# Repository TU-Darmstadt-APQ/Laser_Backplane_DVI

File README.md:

# Laser Head with fast Modulation Input
This repository contains the [KiCad](https://www.kicad.org/) design files for a compact laser backplane with a DVI connector for application in an ECDL laser system. The laser backplane features a fast current modulation input designed for large-bandwidth laser-frequency stabilization and a laser diode protection circuit. An additional connector for the laser piezo actuator is available.

## Laser diode protection circuit
The protection circuit consists of a relay and a reverse protection diode. The latching relay shorts the laser diode whenever the cable is disconnected or the current driver is turned off. In order to reduce the relay idle current, a latching relay and circuit are used. A fast switching transistor is used as reverse protection diode. The transistor features a very low reverse current leakage and a fast reverse recovery time.

## Fast Current Modulation
The fast modulation input consists of a Howland Current Pump complemented by a passive impedance matching network (see related work for details). It features:
- 3 dB gain flatness DC to 100 MHz
- Phase lag below 90° up to 25 MHz
- Transconductance gain of 1 mA / V
- Input voltage range ±4.8 V

**Note on the compliance voltage**
The compliance voltage of the Howland Current Pump is half of the positive output voltage swing of the operational amplifier. The circuit is implemented by a rail-to-rail output operational amplifier (ADA4807) supplied by ±5 V. Hence, the voltage at the laser diode anode is limited to 2.4 V accounting for a small head-room. Some additional head-room should be reserved for the (small) rise of the voltage required for the maximal output of the current source (5 mA). The maximal laser diode anode voltage is sufficient as a compliance voltage for infra red laser diodes. 

## Pin Configuration

Connector: DVI-I Dual Link (female)

| Pin 		| Signal 		| Description 	|
| --- 		| --- 			|	---			|
|  1 to 5 	|	NC			|				|
|  6  		|	-12 V		|	Negative supply for fast current modulation: -20 V to -5.5 V / 10 mA (max.)	|
|  7		|	EEPROM		|	Optional single wire EEPROM: AT21CS11	|
|  8  		| NC 			|				|
|  9  		| Ld-			| Laser diode cathode current pin 1/2	|
|  10  		| LD+			| Laser diode anode current pin 1/2		|
|  11  		| NC			|				|
|  12  		| Ld-			| Laser diode cathode current pin 2/2	|
|  13  		| LD+			| Laser diode anode current pin 2/2		|
|  14  		|	+12 V		| Positive supply for fast current modulation and protection circuit: 7 V to 18 V / 50 mA (max.) 	|
|  15  		| GND			| Ground reference for power supply	and modulation circuit  |
|  16  		| Relay-		| Connect to GND to switch the relay to 'laser on' state		|
|  17 to 22	| NC			| 				|
|  23  		| V_diode+		| Laser anode voltage sense connection		|
|  24  		| V_diode-		| Laser cathode voltage sense connection	|
|  C1 to C5	| NC			| 				|
|  SH		| NC			| 	Connect the shield to the laser case only			|

## Design Files
The design files can be found on the [releases](../../releases) page and include the following resources:

- Schematics as a PDF
- Gerber files
- Pick & place position files
- Bill of materials as a CSV file and also as an interactive HTML version

The latest revision of those files can be found [here](../../releases/latest).

## Related Work
Review of Scientific Instruments **93**, 063002 (2022); https://doi.org/10.1063/5.0093520

arXiv:2203.06097 [physics.optics]; [https://arxiv.org/abs/2203.06097](https://arxiv.org/abs/2203.06097)

T. Preuschoff, *Laser Technologies for Applications in Quantum Information Science*, Ph.D. thesis, TU Darmstadt, 2023, [10.26083/tuprints-00023242](10.26083/tuprints-00023242)

## License
This work is released under the CERN-OHL-W
See [https://ohwr.org/cern_ohl_w_v2.pdf](https://ohwr.org/cern_ohl_w_v2.pdf) or the included LICENSE file for more information.

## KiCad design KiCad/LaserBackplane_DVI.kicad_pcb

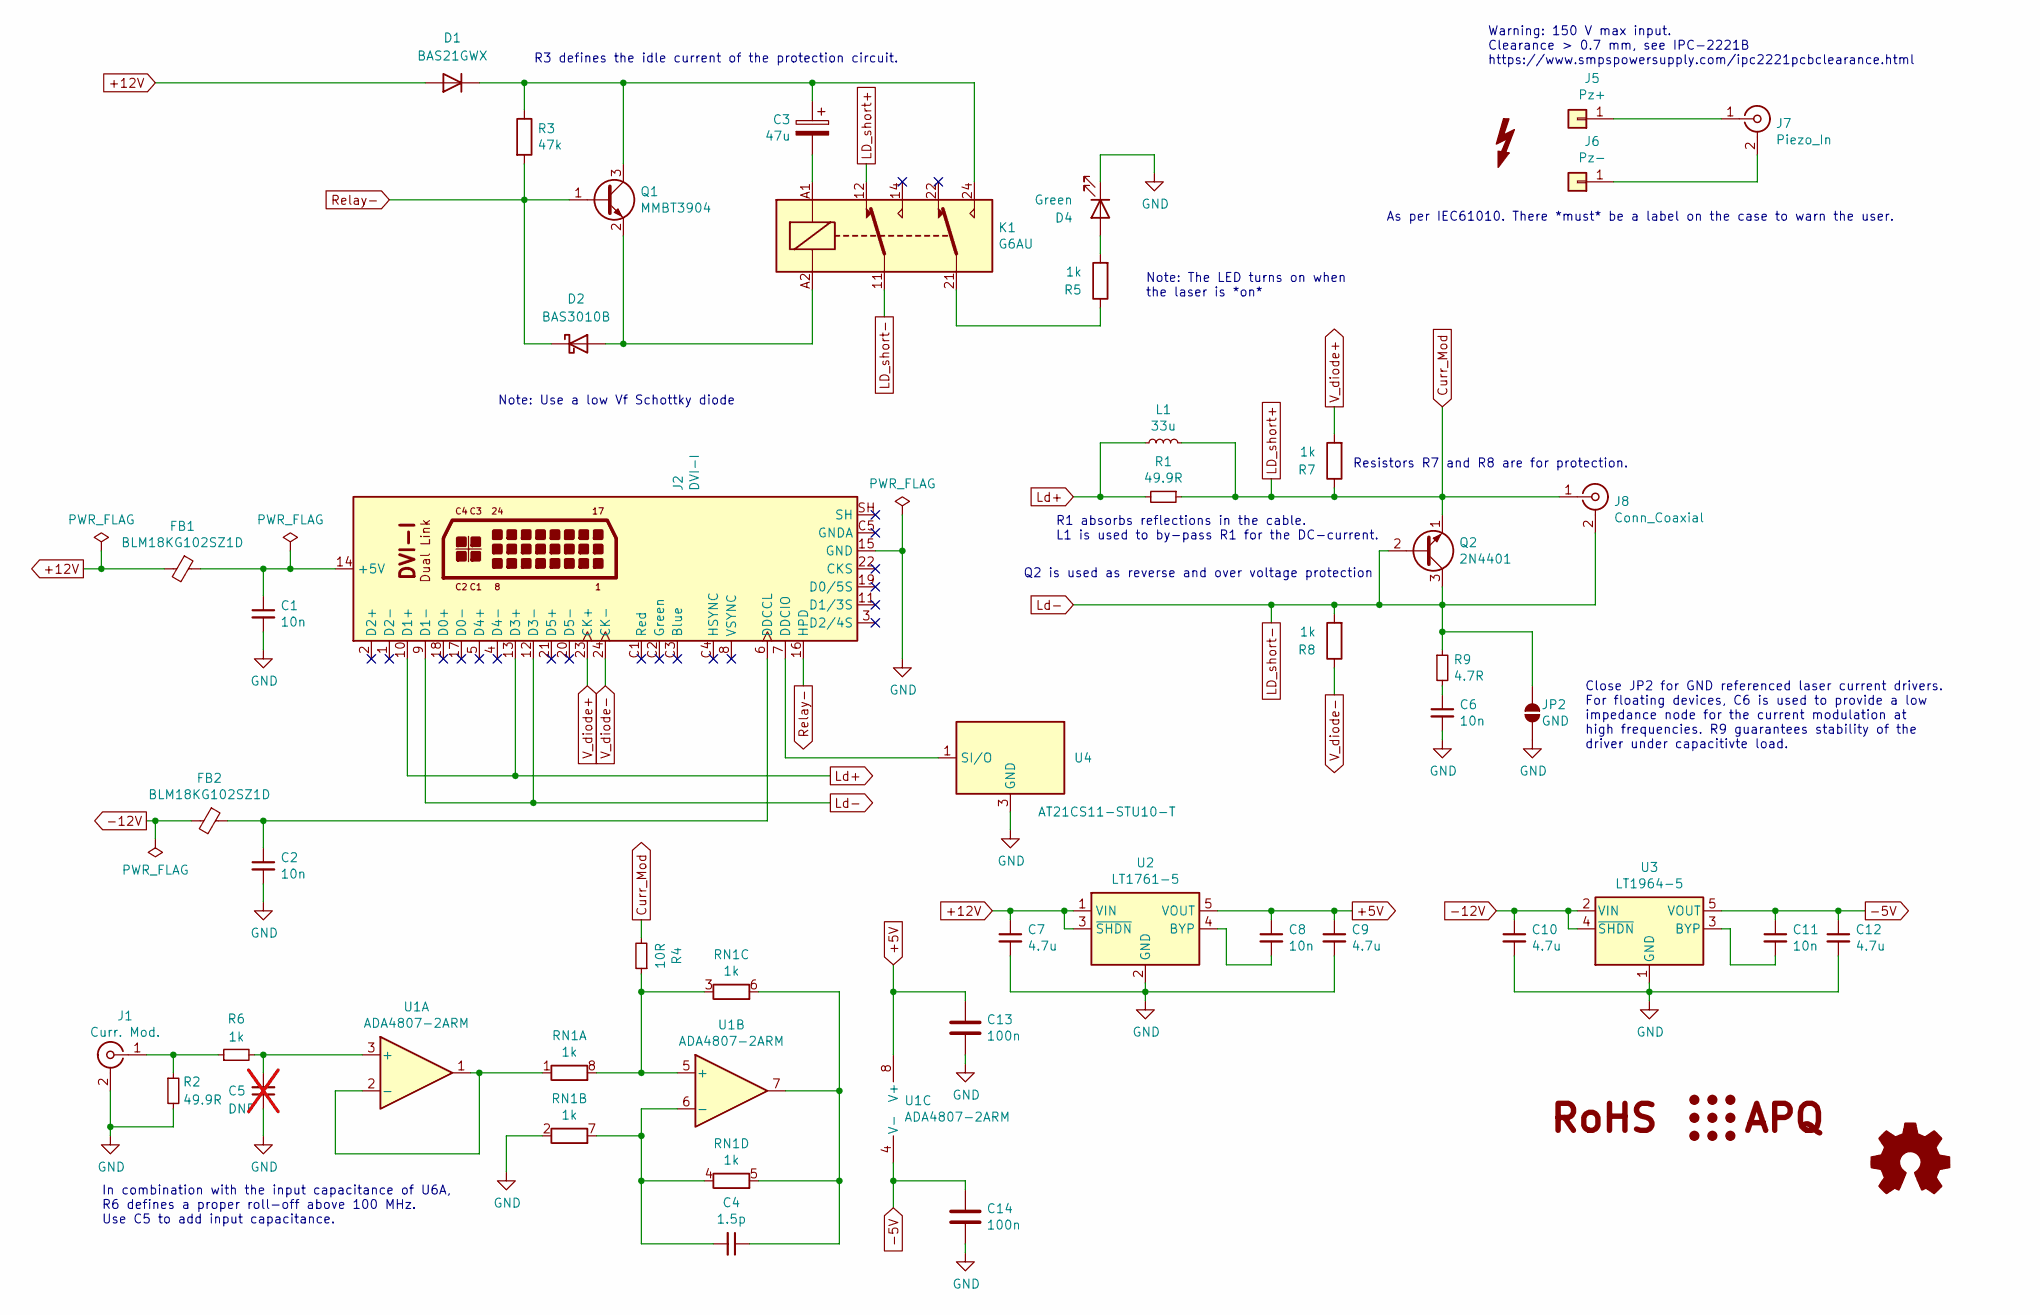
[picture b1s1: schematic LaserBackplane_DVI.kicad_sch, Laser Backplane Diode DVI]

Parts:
C1, C2, C6, C8, C11: 10n; C_0603_1608Metric
C3: 47u; CP_Radial_D5.0mm_P2.00mm
C4: 1.5p; C_0603_1608Metric
C5: DNF; C_0603_1608Metric; not fitted
C7, C9, C10, C12: 4.7u; C_0805_2012Metric
C13, C14: 100n; C_0603_1608Metric
D1: BAS21GWX; D_SOD-123
D2: BAS3010B; D_SOD-323
D4: Green; LED_D3.0mm_FlatTop
FB1, FB2: BLM18KG102SZ1D; L_0603_1608Metric
J1: Curr. Mod.; SMA_Amphenol_132291_Vertical
J2: DVI-I; DVI-I_Conn-Link_CDVI-F29VDG1-P1_Vertical
J5: Pz+; TestPoint_Keystone_5015_Micro_Mini
J6: Pz-; TestPoint_Keystone_5015_Micro_Mini
J7: Piezo_In; SMA_Amphenol_132291_Vertical
J8: Conn_Coaxial; SMP_TE_CONSMP001-SMD-G-T_Vertical
JP2: GND; SolderJumper-2_P1.3mm_Open_RoundedPad1.0x1.5mm
K1: G6AU; Relay_DPDT_Omron_G6A
L1: 33u; Coilcraft_XGL5050
LOGO1: Logo_APQ; APQ-Logo_small
LOGO2: Logo_Open_Hardware_Small; OSHW-Logo_7.5x8mm_SilkScreen
LOGO3: Logo_RoHS; RoHS-Logo_6mm_SilkScreen
Q1: MMBT3904; SOT-23
Q2: 2N4401; TO-92_Inline_Horizontal1
R1: 49.9R; R_0805_2012Metric
R2: 49.9R; R_0612_1632Metric
R3: 47k; R_0603_1608Metric
R4: 10R; R_0603_1608Metric
R5, R6, R7, R8: 1k; R_0603_1608Metric
R9: 4.7R; R_0603_1608Metric
RN1: 1k; MSOP-8_3x3mm_P0.65mm
SYM1: SYM_Flash_Small; Symbol_HighVoltage_Triangle_3x3mm
U1: ADA4807-2ARM; MSOP-8_3x3mm_P0.65mm
U2: LT1761-5; TSOT-23-5
U3: LT1964-5; TSOT-23-5
U4: AT21CS11-STU10-T; SOT-23

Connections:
+5V: C8.1, C9.1, C13.1, U1.8 (V+), U2.5 (VOUT)
+12V: C7.1, D1.2 (A), FB1.2, U2.1 (VIN), U2.3 (~SHDN)
-5V: C11.1, C12.1, C14.1, U1.4 (V-), U3.5 (VOUT)
-12V: C10.1, FB2.2, U3.2 (VIN), U3.4 (~SHDN)
Curr_Mod: J8.1 (In), K1.12, L1.2, Q2.1 (E), R1.1, R4.2, R7.1
GND: C1.2, C2.2, C5.1, C6.2, C7.2, C9.2, C10.2, C12.2, C13.2, C14.2, D4.1 (K), J1.2 (Ext), J2.15 (GND), JP2.2 (B), R2.2, RN1.2 (R2.1), U2.2 (GND), U3.1 (GND), U4.3 (GND)
LD_short-: J2.9 (D1-), J2.12 (D3-), J8.2 (Ext), JP2.1 (A), K1.11, Q2.2 (B), Q2.3 (C), R8.2, R9.1
Ld+: J2.10 (D1+), J2.13 (D3+), L1.1, R1.2
unnamed: C3.2, K1.A1
unnamed: C6.1, R9.2
unnamed: C3.1, D1.1 (K), K1.24, Q1.3 (C), R3.1
unnamed: D2.2 (A), K1.A2, Q1.2 (E)
unnamed: D4.2 (A), R5.2
unnamed: J1.1 (In), R2.1, R6.1
unnamed: C1.1, FB1.1, J2.14 (+5V)
unnamed: C2.1, FB2.1, J2.6 (DDCCL)
unnamed: J2.7 (DDCIO), U4.1 (SI/O)
unnamed: J5.1, J7.1 (In)
unnamed: J6.1, J7.2 (Ext)
unnamed: K1.21, R5.1
unnamed: RN1.1 (R1.1), U1.1, U1.2 (-)
unnamed: R4.1, RN1.3 (R3.1), RN1.8 (R1.2), U1.5 (+)
unnamed: C4.2, RN1.4 (R4.1), RN1.7 (R2.2), U1.6 (-)
unnamed: C4.1, RN1.5 (R4.2), RN1.6 (R3.2), U1.7
unnamed: C5.2, R6.2, U1.3 (+)
unnamed: C8.2, U2.4 (BYP)
unnamed: C11.2, U3.3 (BYP)
Relay-: D2.1 (K), J2.16 (HPD), Q1.1 (B), R3.2
V_diode+: J2.23 (CK+), R7.2
V_diode-: J2.24 (CK-), R8.1

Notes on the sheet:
R3 defines the idle current of the protection circuit.
Note: The LED turns on when the laser is *on*
Warning: 150 V max input. Clearance > 0.7 mm, see IPC-2221B https://www.smpspowersupply.com/ipc2221pcbclearance.html
Close JP2 for GND referenced laser current drivers. For floating devices, C6 is used to provide a low impedance node for the current modulation at high frequencies. R9 guarantees stability of the driver under capacitivte load.
R1 absorbs reflections in the cable. L1 is used to by-pass R1 for the DC-current.
In combination with the input capacitance of U6A, R6 defines a proper roll-off above 100 MHz. Use C5 to add input capacitance.
Q2 is used as reverse and over voltage protection
Note: Use a low Vf Schottky diode
Resistors R7 and R8 are for protection.
As per IEC61010. There *must* be a label on the case to warn the user.

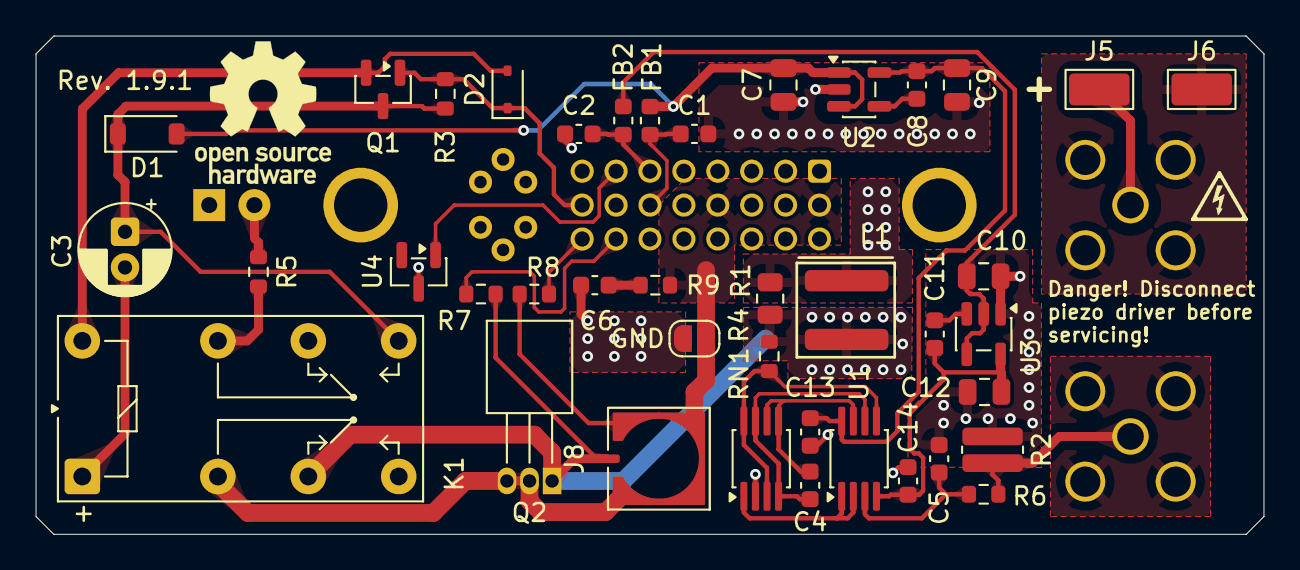
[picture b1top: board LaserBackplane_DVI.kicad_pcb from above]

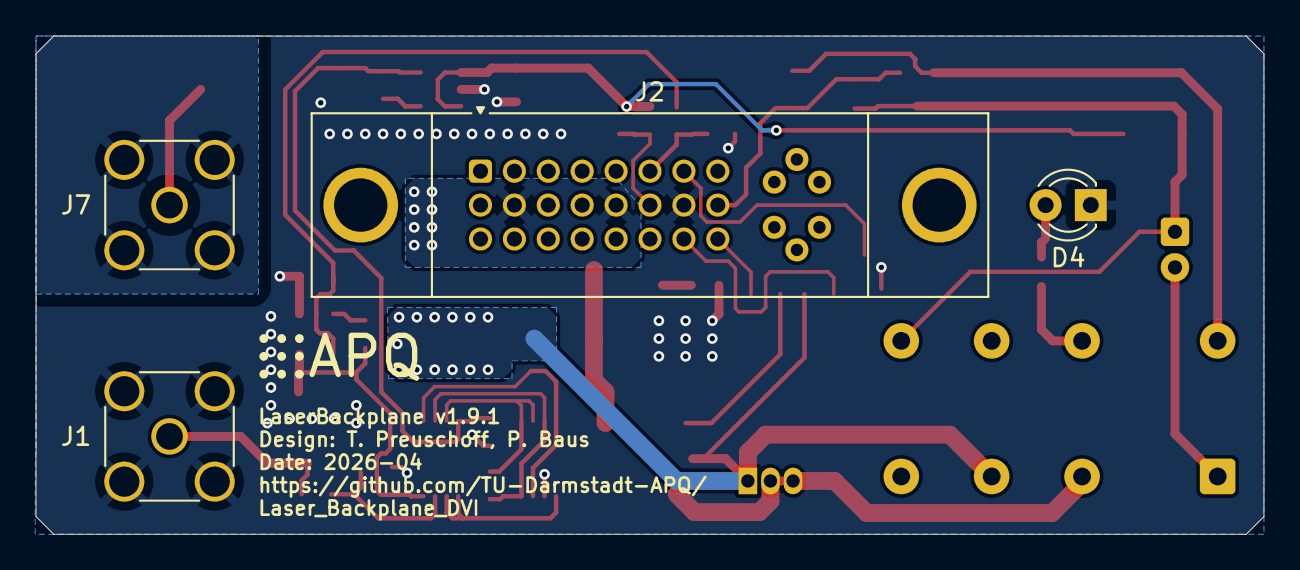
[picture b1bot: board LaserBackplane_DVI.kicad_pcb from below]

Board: 2 copper layers, 69.0 x 28.0 mm, 47 parts (5 on the bottom side), 30 nets.

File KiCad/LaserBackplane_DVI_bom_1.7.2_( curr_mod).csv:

Component,Quantity Per PCB,References,Value,MFN,PN,Description,Footprint,RoHS,Temperature,Note,Alternative
1,1,C4,1.5p,Yageo,CC0603CPNPO9BN1R5,"Unpolarized capacitor, small symbol",C_0603_1608Metric,,,,
2,2,C1-C2,10n,Kemet,C0603C103K2RECAUTO,"Unpolarized capacitor, small symbol",C_0603_1608Metric,,,,
3,3,C6  C8  C11,10n,Murata Electronics,GRM1885C1H103JA01J,"Unpolarized capacitor, small symbol",C_0603_1608Metric,,,,
4,4,C7  C9-C10  C12,4.7u,Murata Electronics,GRM21BR61H475KE51L,"Unpolarized capacitor, small symbol",C_0805_2012Metric,,,,
5,1,C3,47u,Nichicon,UHV1V470MDD,Polarized capacitor,CP_Radial_D5.0mm_P2.00mm,,,,
6,1,D1,BAS21GWX,Nexperia,BAS21GWX,Diode,D_SOD-123,,,,
7,1,D2,BAT54,STMicroelectronics,BAT54SFILMY,Schottky diode,D_SOT-23_ANK,,,Use a low Vf Schottky,
8,1,D4,Green,Kingbright,WP424GDT,Light emitting diode,LED_D3.0mm_FlatTop,,,,
9,2,FB1-FB2,BLM18KG102SZ1D,Murata,BLM18KG102SZ1D,"Ferrite bead, small symbol",L_0603_1608Metric,,,,
10,2,J1  J7,Curr. Mod.,Amphenol,132291,"coaxial connector (BNC, SMA, SMB, SMC, Cinch/RCA, LEMO, ...)",SMA_Amphenol_901-144_Vertical,,,,
11,1,J2,DVI-I,Conn_Link,CDVI-F29VDG1-P1,DVI-I dual link connector,DVI-I_Conn_Link_CDVI-F29VDG1-P1,,,,
12,1,K1,G6AU,Omron,G6AU-274P-ST-US-DC9,"Omron Low Signal Relay, Single-winding latching type",Relay_SPDT_OMRON-G6A,,,,
13,1,L1,33u,Coilcraft,XGL5050-333MEC,"Inductor, small symbol",Coilcraft_XGL5050,,,,Coilcraft XAL5050-223MEC
14,1,Q2,2N4401,ON Semiconductor,2N4401BU,"NPN transistor, emitter/base/collector",TO-92_Inline_Horizontal1,,,,
15,1,Q1,MMBT3904,Nexperia,MMBT3904VL,"0.2A Ic, 40V Vce, Small Signal NPN Transistor, SOT-23",SOT-23,,,,
16,1,R9,4.7,Panasonic,ERJ-3RQF4R7V,"Resistor, small symbol",R_0603_1608Metric,,,,
17,1,R4,10,Susumu,RR0816Q-100-D,"Resistor, small symbol",R_0603_1608Metric,,,,
18,1,R1,49.9,Susumu,RR0816Q-49R9-D-68R,"Resistor, small symbol",R_0603_1608Metric,,,,
19,1,R2,49.9,Yageo,RC1210FR-0749R9L,"Resistor, small symbol",R_1210_3225Metric,,,,
20,4,R5-R8,1k,Susumu,RR0816P-102-D,Resistor,R_0603_1608Metric,,,,
21,1,R3,100k,Susumu,RR0816P-104-D,Resistor,R_0603_1608Metric,,,,
22,1,RN1,1k,Vishay,MORNTA1001AT5,"4 resistor network, parallel topology, split",MSOP-8_3x3mm_P0.65mm_mod,,,,
23,1,U1,ADA4807-2ARM,Analog Devices,ADA4807-2ARMZ,"Dual Rail-to-Rail Input/Output Amplifiers, MSOP-8",MSOP-8_3x3mm_P0.65mm_mod,,,,
24,1,U2,LT1761-5,Analog Devices,LT1761ES5-5#TRPBF,"MICROPOWER Low Noise 5V 100mA LDO regulator, TSOT-23-5",TSOT-23-5,,,,
25,1,U3,LT1964-5,Analog Devices,LT1964ES5-5#TRPBF,"MICROPOWER 200mA Low Noise LDO negative regulator, fixed output -5V, TSOT-23-5",TSOT-23-5,,,,





Component Groups:,29
Component Count:,40
Fitted Components:,36
Number of PCBs:,1
Total components:,36
Schematic Version:,1.7.2
Schematic Date:,2023-11-02
PCB Variant:,curr_mod
BoM Date:,02.11.2023 14:00:07
Schematic Source:,LaserBackplane_DVI.kicad_sch
KiCad Version:,Eeschema (6.0.7)

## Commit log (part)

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2021-03-04 Ld-: SMD Pad for shield
    Fix footprints and replace Ld- THT with SMD pad
2021-03-15 Incomplete: Add current source
2021-03-18 Add current source
    Replace Bias-T with Howland current source. The current source requires additional negative supply (Pin7).
    Replace large resistors with inductors+49.9-resistors.
2021-07-23 Update BOM
2021-07-23 Fix laser diode polarity
    Switch LD-/LD+ pins at the DVI connector
2021-08-20 Update images and pdf schematic
2021-10-11 Remove L2
    Remove inductance and bypass resistor at Ld-.
2021-11-02 SMD solder pads for piezo connection
2021-12-16 Current modulation: add input series resitance for proper roll-off and capacitance at Ld- for flat response.
2022-01-25 Update to KiCad6
2022-01-25 Update gerber files
2022-01-28 Update DVI connector 3D model
2022-02-21 Rename project files
2022-03-01 Update 3D models
2022-05-06 Add alternative part for inductor.
2023-10-27 Added CI pipeline
2023-10-27 Fixed file names
2023-10-27 Rerun CI if the config changes
2023-10-27 Fix regex
2023-10-27 Update DRC filter
2023-10-27 Remove unused variants
2023-10-27 Fix outputs
2023-10-27 Require tests
2023-10-28 Removed unused modules
2023-11-02 Add variants ('default': without current mod., 'curr_mod': with current mod.)
2023-11-03 Remove production files
2023-11-03 Added variants
2023-11-03 Update CI workflow
2023-11-03 Update labels and PCB images
2023-11-03 Update README.md
    Removed KiCad version number
2023-11-05 Updated to KiCad 7 Updated footprints
2023-11-05 Added 3d model to XAL5050 inductor
2023-11-05 Suppress DRC error caused by the XAL5050 model
2023-11-20 Add back panel
2023-11-20 Update PCB images
2023-11-23 Added remaining authors
2023-12-15 [gha] Bump actions/download-artifact from 3 to 4
    Bumps [actions/download-artifact](https://github.com/actions/download-artifact) from 3 to 4.
    - [Release notes](https://github.com/actions/download-artifact/releases)
    - [Commits](https://github.com/actions/download-artifact/compare/v3...v4)
    ---
    updated-dependencies:
    - dependency-name: actions/download-artifact
2023-12-17 Updated to actions/download-artifact@v4
2024-05-12 Update to KiCad 8 Removed obsolete libs and footprints
2024-05-12 Replaced EOL parts
2024-05-12 Updated CI
2024-05-12 Update PCB from schematic
2024-05-12 Cleanup
2024-05-13 Updated parts
    - Swapped 50 ohm resistor for a higher wattage part
    - Added bypass capacitors to the current source opamp
    - Put all parts on a 0.25 mm grid
    - Improved routing
    - Removed ground layer keepout below the current source, because there is no significant coupling at 1.6 mm distance
    - Added RoHS information
2024-05-13 Update CI actions actions/upload-artifact and actions/download-artifact to v4. This supersedes https://github.com/TU-Darmstadt-APQ/Laser_Backplane_DVI/pull/3 and https://github.com/TU-Darmstadt-APQ/L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
2024-05-13 Place bypass capacitors only when using the current mod variant
2024-05-14 Bump version to 1.7.4
2024-05-14 Update README.md
    Add whitespace to push DVI connector pinout to the next line
2024-05-14 Add chamfer to corners
2024-05-14 Add teardrops
2024-05-14 Added peizo driver high voltage warning
2024-05-14 Cleaned up labels
2024-05-14 Create individual gerber files for all variants to make sure DNP parts are not included in the mask layer
2024-05-14 Bump version to 1.8.0
2024-05-15 Updated DVI connector footprint
2024-10-18 1.7.4 (#5)
    * Add chamfer to corners
    * Change line with of the part dimentsions to 0.1 mm
    * Add teardrops
    * Added peizo driver high voltage warning
    * Add PCBA variant
    * Cleaned up labels
2025-02-16 Replaced 10nF X7R CGA3E2X7R1H103K080AA with C0G CGA3E2C0G1H103J080AE
2025-02-16 Updated libs
2025-02-16 Updaed LED footprint
2025-02-17 Replaced X7R 10nF Capacitors with C0G (#6)
    * Replaced 10nF X7R CGA3E2X7R1H103K080AA with C0G CGA3E2C0G1H103J080AE
    * Added letter "R" to resistor values that do not have an SI suffix
    * Updated LED footprint for KiCAD 8.0.8
    * Added missing high voltage footprint
2025-06-24 Bump to KiCad 9
2025-06-24 Update/kicad9 (#7)
    * Bump to KiCad 9
    * Bump version to 1.8.0
2025-06-24 Updated DVI connector footprint (#8)
2025-06-26 Changed laser diode connector form solder connection to SMP (#9)
2025-06-26 Removed paste layer from piezo solder pads (#10)
2025-06-26 Updated PCB
2025-06-26 Fixed SMP connector symbol. Removed incorrect 3D model (#11)
    * Fixed SMP connector symbol. Removed incorrect 3D model
2025-06-26 Drop relay 3d model no longer needed (#13)
2025-06-26 Removed incorrect 3D model from the DVI connector
2025-06-26 Added 3D model for the DVI connector Replaced SMA connector footprint with correct one
2025-06-26 Fixed references
2025-06-26 Fixed gerber file generation
2025-06-26 Fixed gerber file generation (#14)
2025-06-26 Do not place the LED for assembly as this needs to match the frontpanel mounting hole (#15)
2025-06-26 Change R3 from 100k to 47k to increase the current through the relay during switch off
2025-06-26 Bump to 1.8.1
    Updated authors
2025-06-26 Bump to 1.8.1 (#17)
    Updated authors
2025-06-27 Correctly skip ERC/DRC when requested
2025-06-27 Add more ERC/DRC warning filters
2025-06-27 Fixed variant
2025-06-27 Add variant fields to PCB
2025-06-27 Fixed incorrect version label
2025-06-27 Refilled zones
2025-06-27 Fix/version (#19)
    * Fixed incorrect version label
    * Refilled zones
    * Updated images
2025-06-27 Fixed filesnames for the CI
2025-06-27 Skip redundant ERC and DRC steps
2025-06-27 Renamed viewport to 'Readme'
    - Treat ERC warnings as errors
2025-06-28 Fixed product number of the relay. Removed dash before DC9 at the end.
2025-06-28 Fixed product number of the relay (#22)
    - Removed the dash before DC9 at the end of the relay PN.
2025-08-06 [gha] Bump actions/download-artifact from 4 to 5 (#23)
    Bumps [actions/download-artifact](https://github.com/actions/download-artifact) from 4 to 5.
    - [Release notes](https://github.com/actions/download-artifact/releases)
    - [Commits](https://github.com/actions/download-artifact/compare/v4...v5)
    ---
    updated-dependencies:
    - dependency-name: actions/download-artifact
2025-08-12 [gha] Bump actions/checkout from 4 to 5
    Bumps [actions/checkout](https://github.com/actions/checkout) from 4 to 5.
    - [Release notes](https://github.com/actions/checkout/releases)
    - [Changelog](https://github.com/actions/checkout/blob/main/CHANGELOG.md)
    - [Commits](https://github.com/actions/checkout/compare/v4...v5)
    ---
    updated-dependencies:
2025-08-31 Fixed alignment issues
    - Moved the LED D4 up by 0.5 mm to match the DVI connector y position
    - Moved the DVI connector 0.005 mm to the right to center it on the PCB
    - Updated DVI footprint to center it on pin 14
    - Redrawn draces connecting the DVI connector
    - Moved piezo labels slight down and away from the edge
2025-08-31 Updated footprints to latest
2025-08-31 Fixed alignment issues (#25)
    * Fixed alignment issues
    - Moved the LED D4 up by 0.5 mm to match the DVI connector y position
    - Moved the DVI connector 0.005 mm to the right to center it on the PCB
    - Updated DVI footprint to center it on pin 14
    - Redrawn draces connecting the DVI connector
    - Moved piezo labels slighty down and away from the edge
2025-08-31 Updared EEPROM symbol Enabled more ERC rules
2025-09-01 Fixed design issues with the back panel - Replaced Inventor with FreeCad - Added pocket for the through-hole capacitor C3 - Fixed connector dimensions - Changed depth of the pocket to the same depth 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
2025-09-01 Fixed design issues with the back panel (#27)
    - Replaced Inventor with FreeCad
    - Added pocket for the through-hole capacitor C3
    - Fixed connector dimensions
    - Changed depth of the pocket to the same depth for all pockets
    - The second SMA connector is now drilled out by default
2025-09-01 Updated license to OHL 2.0 (#28)
2025-10-27 [gha] Bump actions/upload-artifact from 4 to 5
    Bumps [actions/upload-artifact](https://github.com/actions/upload-artifact) from 4 to 5.
    - [Release notes](https://github.com/actions/upload-artifact/releases)
    - [Commits](https://github.com/actions/upload-artifact/compare/v4...v5)
    ---
    updated-dependencies:
    - dependency-name: actions/upload-artifact
2025-10-27 [gha] Bump actions/upload-artifact from 4 to 5 (#29)
    Bumps [actions/upload-artifact](https://github.com/actions/upload-artifact) from 4 to 5.
    - [Release notes](https://github.com/actions/upload-artifact/releases)
    - [Commits](https://github.com/actions/upload-artifact/compare/v4...v5)
    ---
    updated-dependencies:
    - dependency-name: actions/upload-artifact
2025-10-27 [gha] Bump actions/download-artifact from 5 to 6 (#30)
    Bumps [actions/download-artifact](https://github.com/actions/download-artifact) from 5 to 6.
    - [Release notes](https://github.com/actions/download-artifact/releases)
    - [Commits](https://github.com/actions/download-artifact/compare/v5...v6)
    ---
    updated-dependencies:
    - dependency-name: actions/download-artifact
2025-11-21 [gha] Bump actions/checkout from 5 to 6 (#31)
    Bumps [actions/checkout](https://github.com/actions/checkout) from 5 to 6.
    - [Release notes](https://github.com/actions/checkout/releases)
    - [Changelog](https://github.com/actions/checkout/blob/main/CHANGELOG.md)
    - [Commits](https://github.com/actions/checkout/compare/v5...v6)
    ---
    updated-dependencies:
2025-12-15 [gha] Bump actions/upload-artifact from 5 to 6
    Bumps [actions/upload-artifact](https://github.com/actions/upload-artifact) from 5 to 6.
    - [Release notes](https://github.com/actions/upload-artifact/releases)
    - [Commits](https://github.com/actions/upload-artifact/compare/v5...v6)
    ---
    updated-dependencies:
    - dependency-name: actions/upload-artifact
2025-12-15 [gha] Bump actions/upload-artifact from 5 to 6 (#32)
    Bumps [actions/upload-artifact](https://github.com/actions/upload-artifact) from 5 to 6.
    - [Release notes](https://github.com/actions/upload-artifact/releases)
    - [Commits](https://github.com/actions/upload-artifact/compare/v5...v6)
    ---
    updated-dependencies:
    - dependency-name: actions/upload-artifact
2026-04-14 Bump to KiCad 9.0.7
    Updated to 1.9.1
2026-04-14 [gha] Bump actions/upload-artifact from 6 to 7
    Bumps [actions/upload-artifact](https://github.com/actions/upload-artifact) from 6 to 7.
    - [Release notes](https://github.com/actions/upload-artifact/releases)
    - [Commits](https://github.com/actions/upload-artifact/compare/v6...v7)
    ---
    updated-dependencies:
    - dependency-name: actions/upload-artifact
2026-04-14 [gha] Bump actions/download-artifact from 6 to 8
    Bumps [actions/download-artifact](https://github.com/actions/download-artifact) from 6 to 8.
    - [Release notes](https://github.com/actions/download-artifact/releases)
    - [Commits](https://github.com/actions/download-artifact/compare/v6...v8)
    ---
    updated-dependencies:
    - dependency-name: actions/download-artifact
2026-04-14 [gha] Bump actions/download-artifact from 6 to 8 (#34)
    Bumps [actions/download-artifact](https://github.com/actions/download-artifact) from 6 to 8.
    - [Release notes](https://github.com/actions/download-artifact/releases)
    - [Commits](https://github.com/actions/download-artifact/compare/v6...v8)
    ---
    updated-dependencies:
    - dependency-name: actions/download-artifact
2026-04-14 Bump PCB version

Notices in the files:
KiCad/LaserBackplane_DVI.kicad_pcb:
Copyright (©) 2025, Patrick Baus
